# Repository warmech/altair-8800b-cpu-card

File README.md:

# Altair 8800B CPU Card
This is a reproduction of the MITS Altair 8800B CPU card, with some cleanup to trace routing and pad placement. While there are reproductions of the 8800's CPU card available, the 8800B's CPU card has not (to date) been reproduced. You may be wondering why this version of the Altair's CPU card exists and the original 8800 card is not useable; this is because the architecture of the 8800 and 8800B differ ever so slightly, making each computer's CPU card incompatible with the other without making some hardware changes.

This version of the card incorporates all of the pertinent hardware design of the original 8800B card, but leaves out all of the unnecessary and/or ancillary traces and pads that were placed for potential future development. Orphaned pads, jumpers, and vias have been removed and only two unlabeled jumpers remain in the vicinity of IC "T" near the bottom-left side of the PCB. The goal of this project was not to recreate the card in a 1:1 fashion, as the original PCB was replete with elements that served no discernably meaningful purpose. Instead, this revision offers a nice, clean, annotated PCB for those whose 8800Bs are either missing a CPU card (as mine was) or whose CPU cards are damaged beyond repair.

This design is presently untested and I am awaiting a set to be fabricated. Once I have tested this card in my 8800B, I will update this disclaimer to indicate as much.

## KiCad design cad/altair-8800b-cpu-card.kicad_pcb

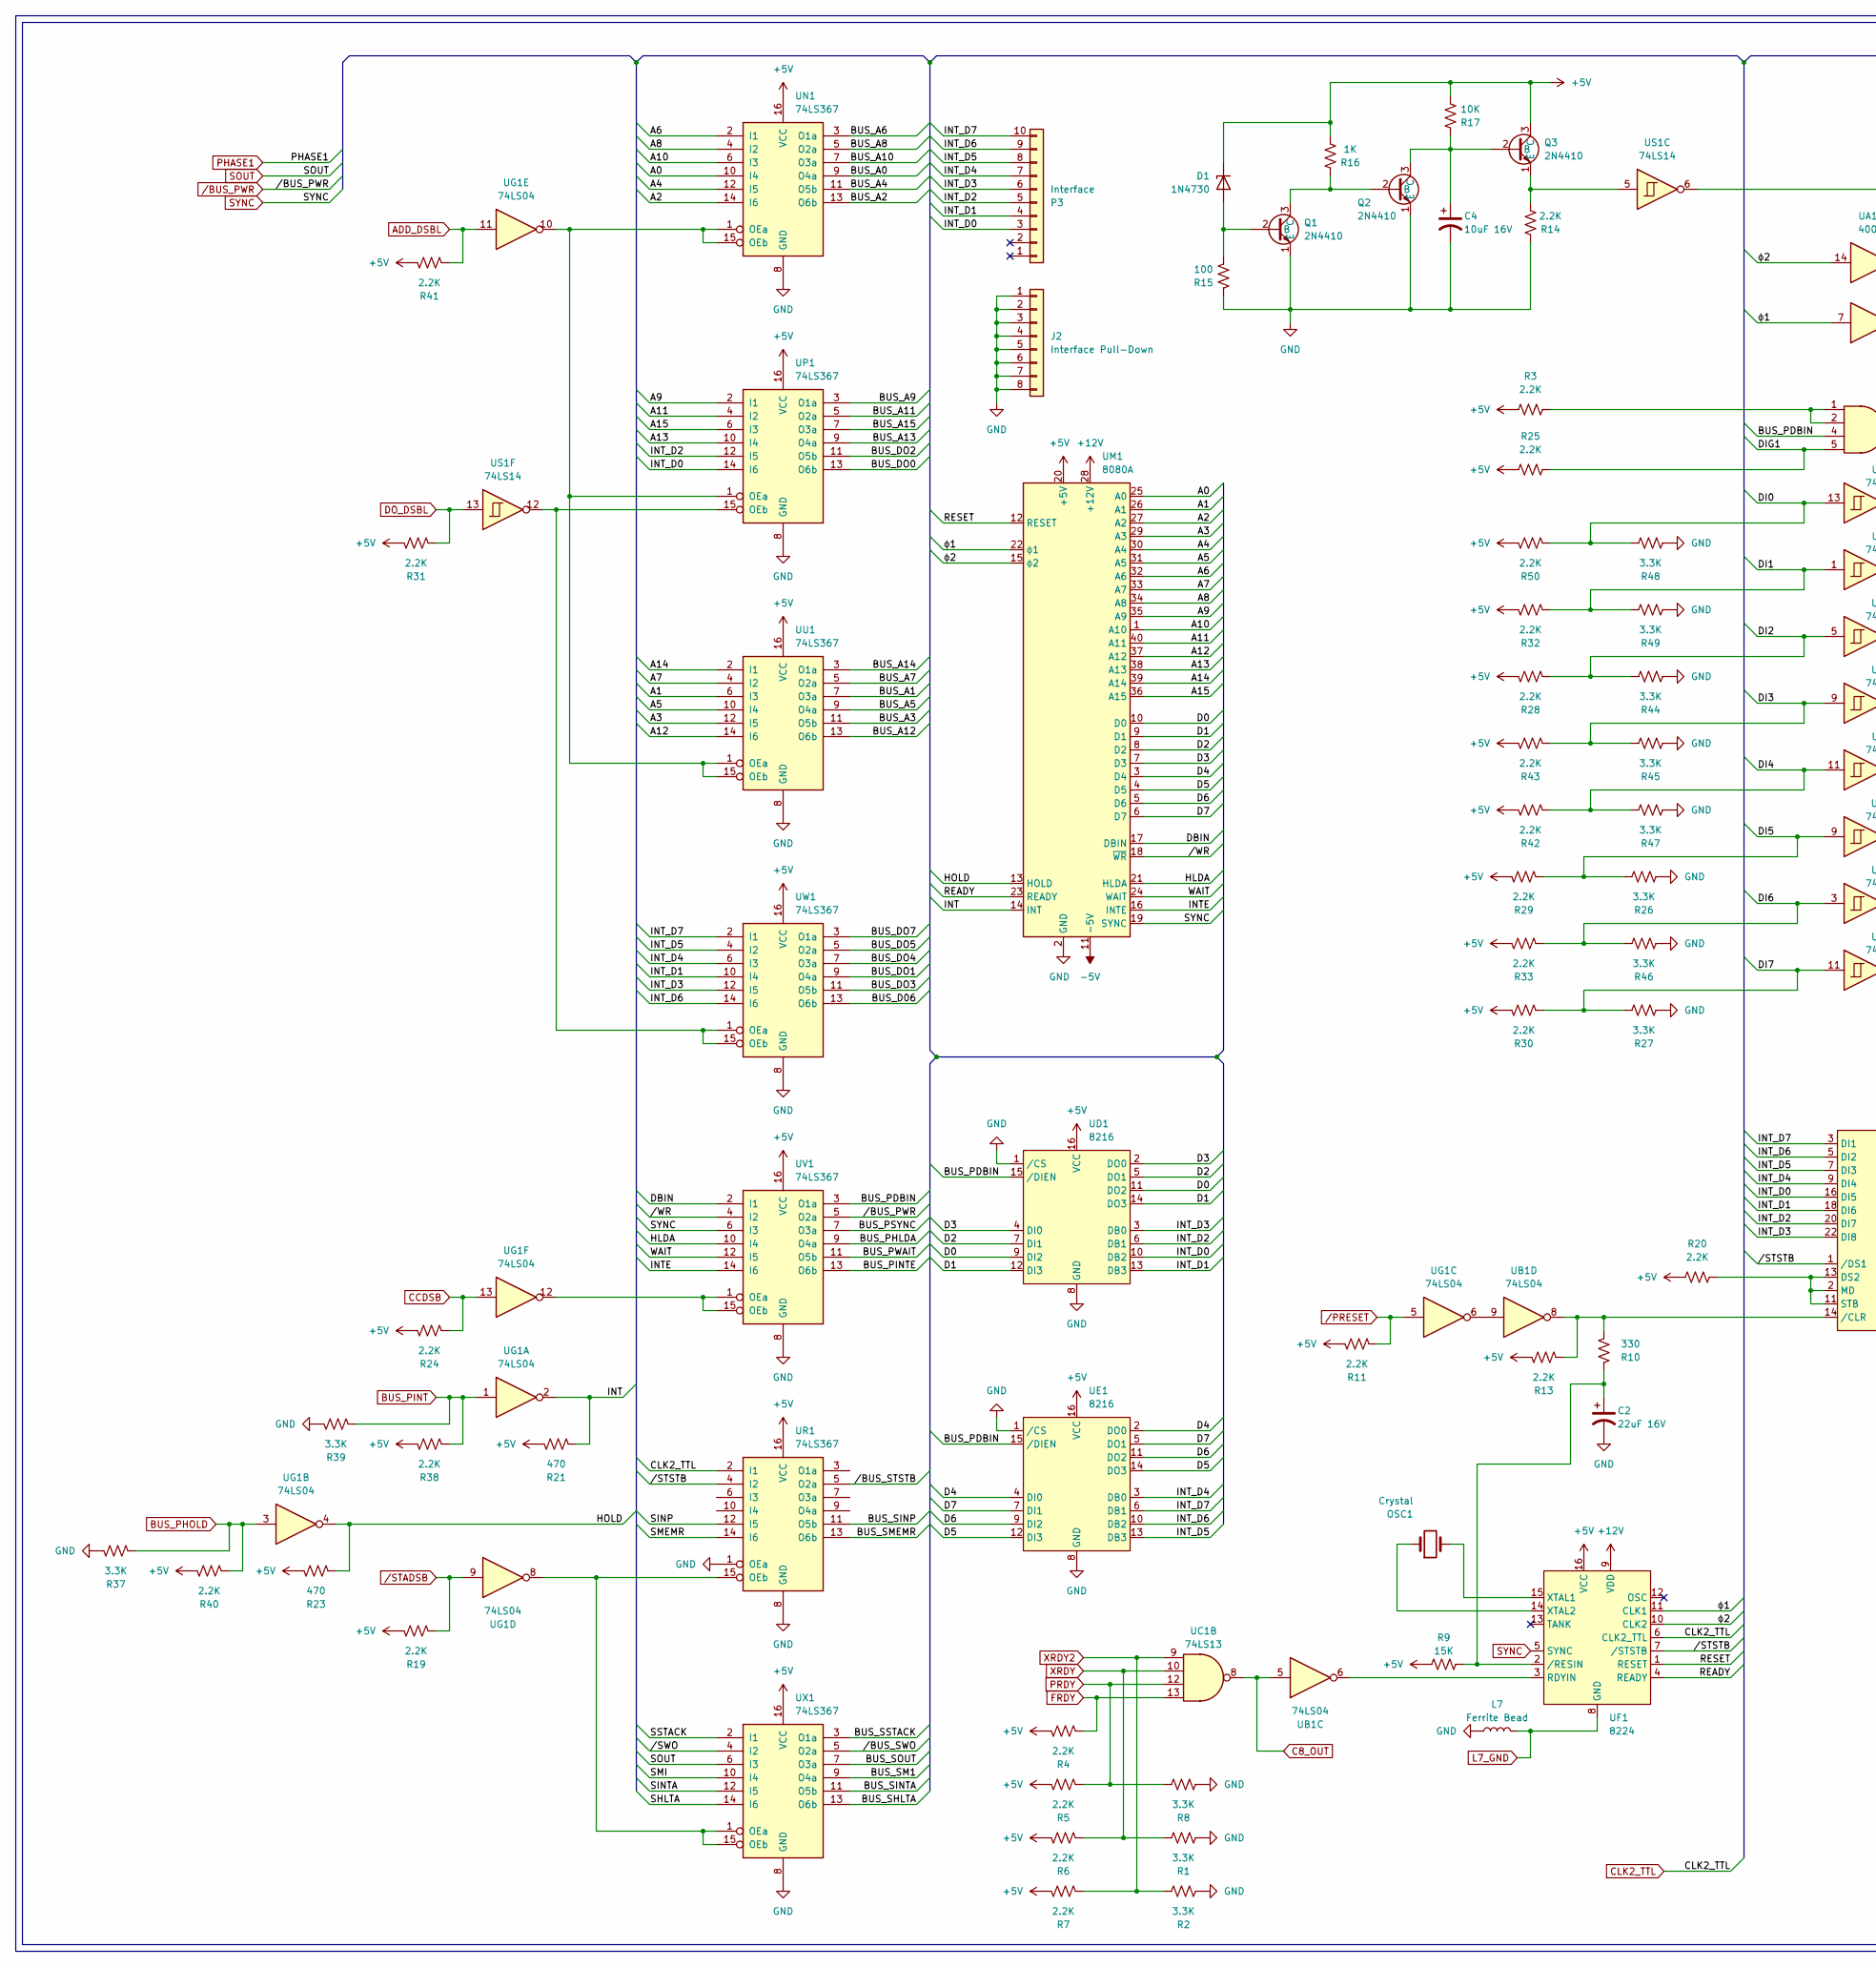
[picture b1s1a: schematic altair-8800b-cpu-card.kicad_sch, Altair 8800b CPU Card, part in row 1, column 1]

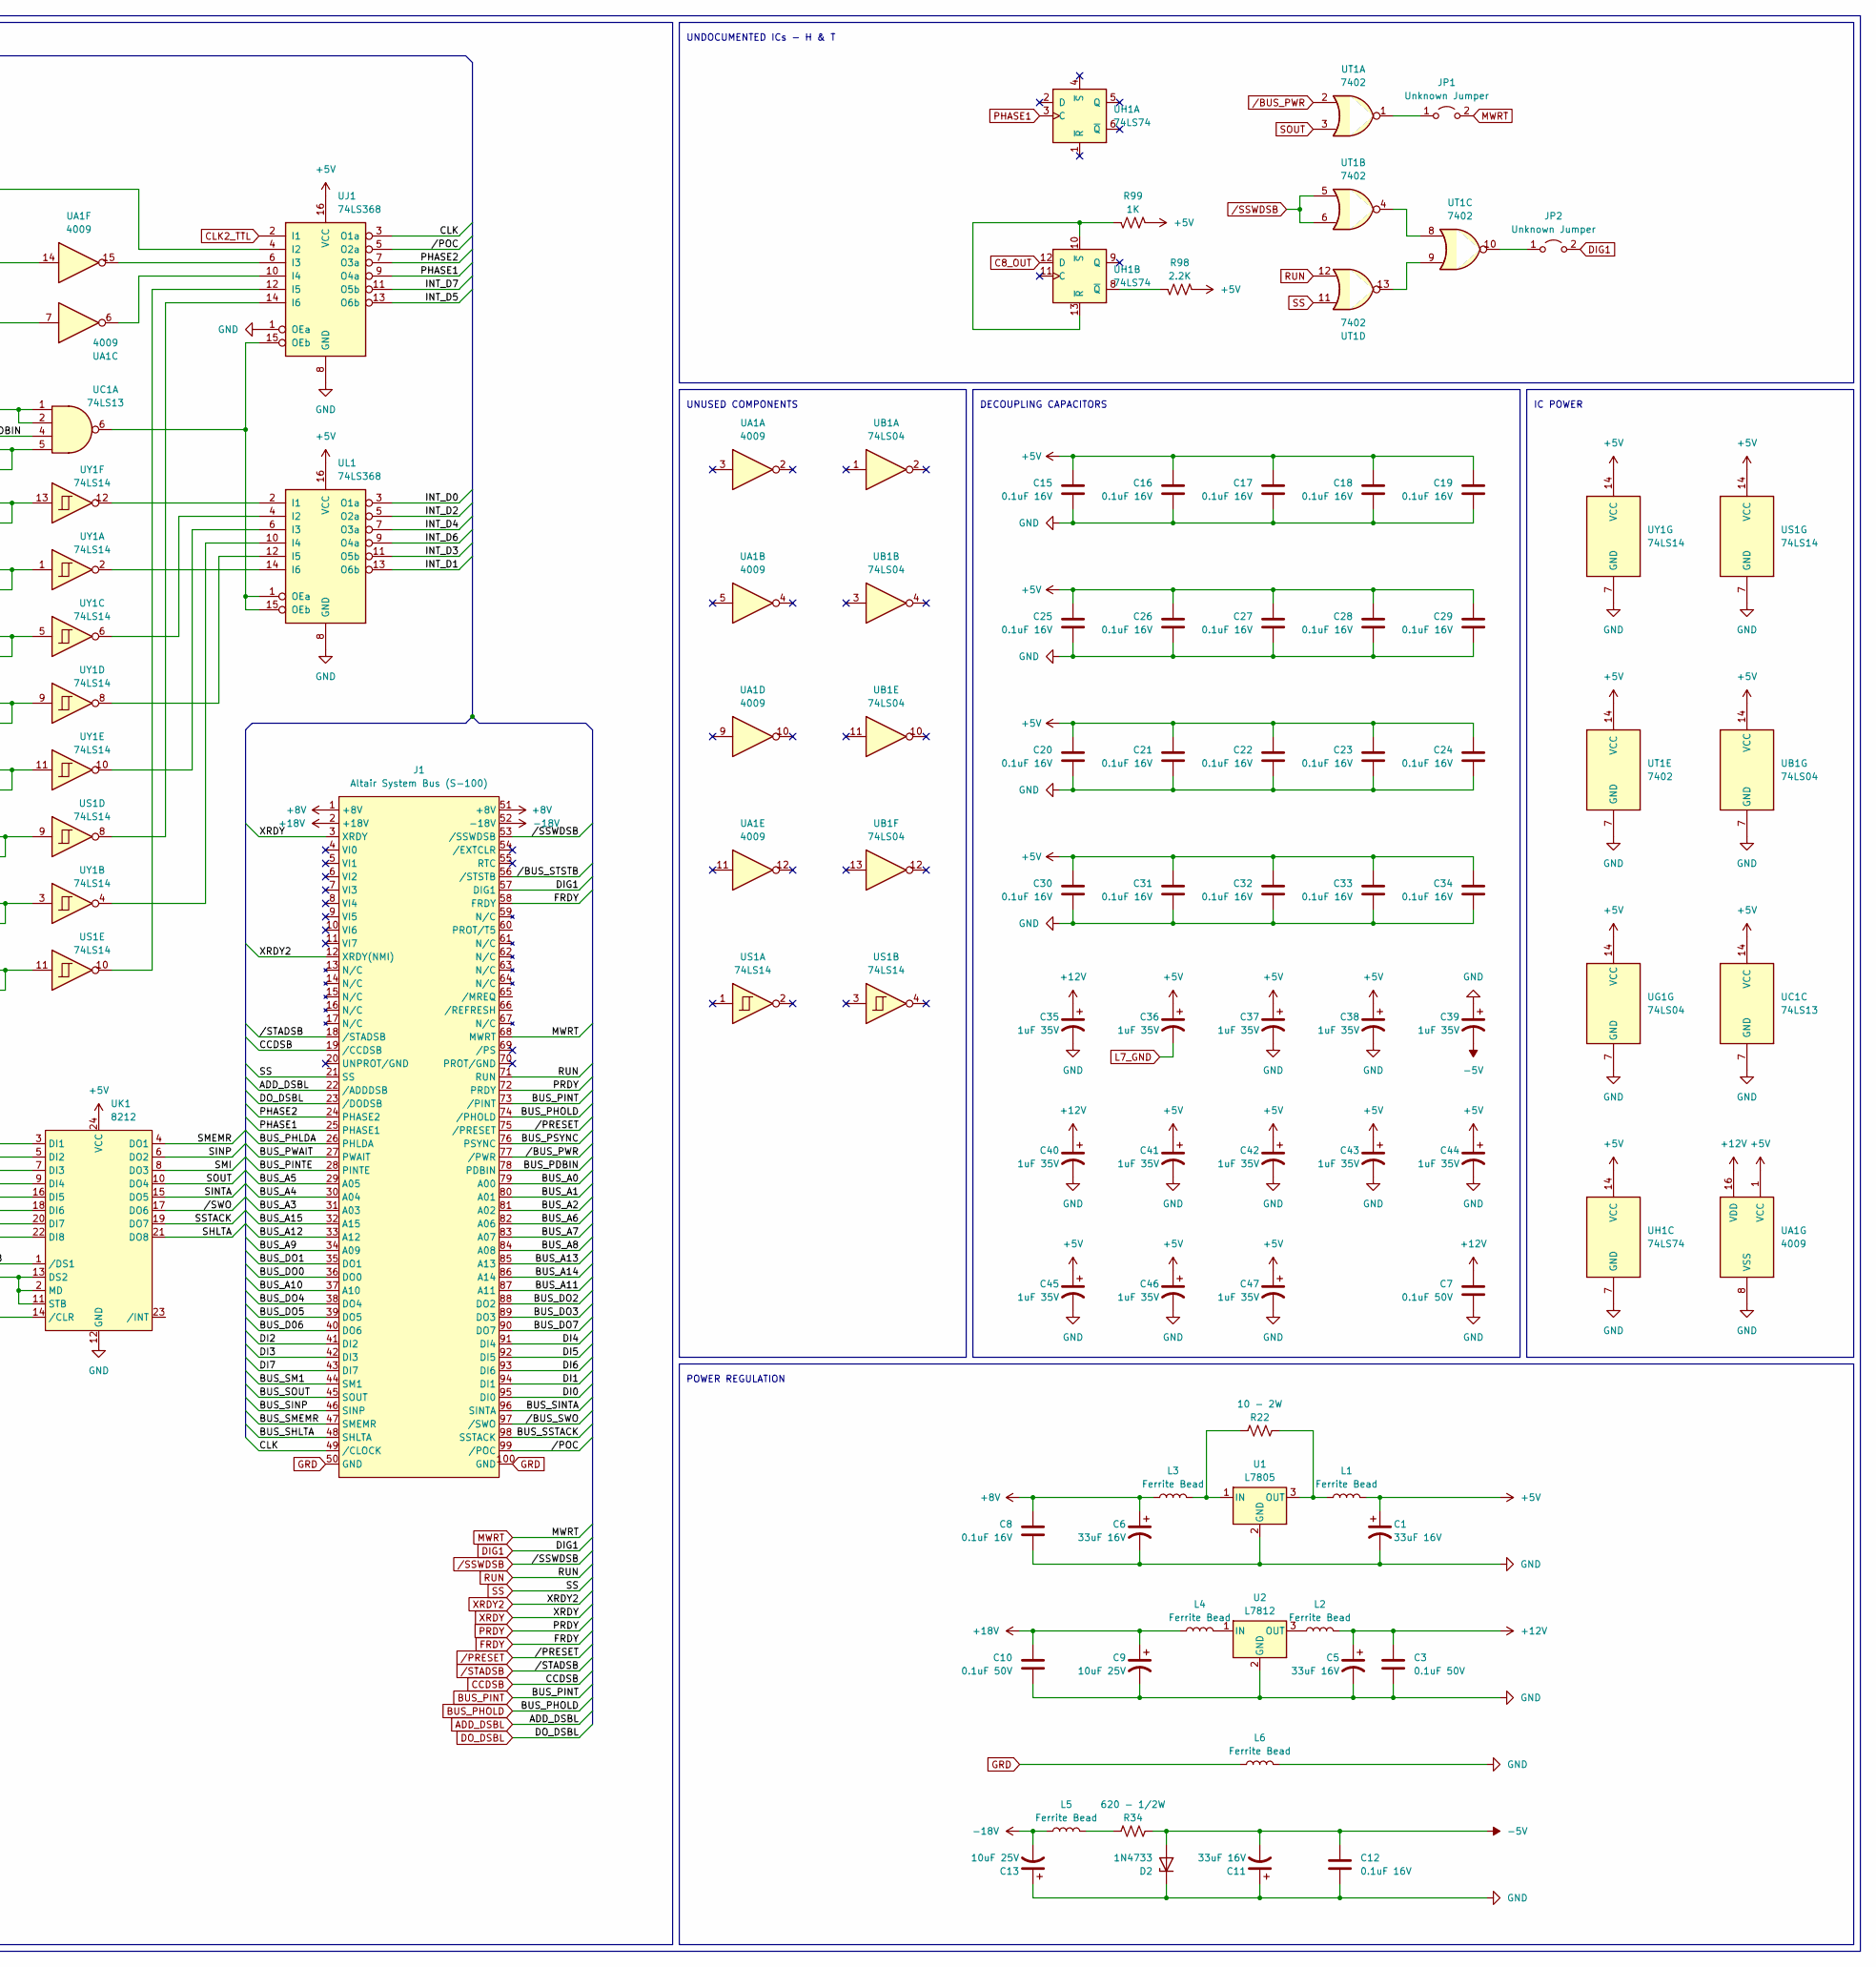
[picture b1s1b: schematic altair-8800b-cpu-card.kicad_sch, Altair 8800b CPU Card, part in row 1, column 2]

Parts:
C1, C5, C6, C11: 33uF 16V; C_Axial_L17.0mm_D6.5mm_P20.00mm_Horizontal
C2: 22uF 16V; CP_Radial_Tantal_D4.5mm_P2.50mm
C3, C7, C10: 0.1uF 50V; C_Rect_L7.0mm_W2.0mm_P5.00mm
C4: 10uF 16V; CP_Radial_Tantal_D4.5mm_P2.50mm
C8, C12, C15, C16, C17, C18, C19, C20, C21, C22, C23, C24, C25, C26, C27, C28, C29, C30, C31, C32, C33, C34: 0.1uF 16V; C_Rect_L7.0mm_W2.0mm_P5.00mm
C9, C13: 10uF 25V; C_Axial_L17.0mm_D6.5mm_P20.00mm_Horizontal
C35, C36, C37, C38, C39, C40, C41, C42, C43, C44, C45, C46, C47: 1uF 35V; CP_Radial_Tantal_D4.5mm_P2.50mm
D1: 1N4730; D_DO-41_SOD81_P10.16mm_Horizontal
D2: 1N4733; D_DO-41_SOD81_P10.16mm_Horizontal
J1: Altair System Bus (S-100); Altair_8800_Bus_Card_Edge
J2: Interface Pull-Down; PinHeader_1x08_P2.54mm_Vertical
JP1, JP2: Unknown Jumper; PinHeader_1x02_P2.54mm_Vertical
L1, L2, L3, L4, L5, L6, L7: Ferrite Bead; L_Axial_L5.3mm_D2.2mm_P7.62mm_Horizontal_Vishay_IM-1
OSC1: Crystal; Crystal_HC49-U_Horizontal
P3: Interface; PinHeader_1x10_P2.54mm_Vertical
Q1, Q2, Q3: 2N4410; TO-92
R1, R2, R8, R26, R27, R37, R39, R44, R45, R46, R47, R48, R49: 3.3K; R_Axial_DIN0207_L6.3mm_D2.5mm_P10.16mm_Horizontal
R3, R4, R5, R6, R7, R11, R13, R14, R19, R20, R24, R25, R28, R29, R30, R31, R32, R33, R38, R40, R41, R42, R43, R50, R98: 2.2K; R_Axial_DIN0207_L6.3mm_D2.5mm_P10.16mm_Horizontal
R9: 15K; R_Axial_DIN0207_L6.3mm_D2.5mm_P10.16mm_Horizontal
R10: 330; R_Axial_DIN0207_L6.3mm_D2.5mm_P10.16mm_Horizontal
R15: 100; R_Axial_DIN0207_L6.3mm_D2.5mm_P10.16mm_Horizontal
R16, R99: 1K; R_Axial_DIN0207_L6.3mm_D2.5mm_P10.16mm_Horizontal
R17: 10K; R_Axial_DIN0207_L6.3mm_D2.5mm_P10.16mm_Horizontal
R21, R23: 470; R_Axial_DIN0207_L6.3mm_D2.5mm_P10.16mm_Horizontal
R22: 10 - 2W; R_Axial_DIN0918_L18.0mm_D9.0mm_P25.40mm_Horizontal
R34: 620 - 1/2W; R_Axial_DIN0207_L6.3mm_D2.5mm_P10.16mm_Horizontal
U1: L7805; TO-220-3_Horizontal_TabDown
U2: L7812; TO-220-3_Horizontal_TabDown
UA1: 4009; DIP-16_W7.62mm
UB1: 74LS04; DIP-14_W7.62mm
UC1: 74LS13; DIP-14_W7.62mm
UD1: 8216; DIP-16_W7.62mm
UE1: 8216; DIP-16_W7.62mm
UF1: 8224; DIP-16_W7.62mm
UG1: 74LS04; DIP-14_W7.62mm
UH1: 74LS74; DIP-14_W7.62mm
UJ1: 74LS368; DIP-16_W7.62mm
UK1: 8212; DIP-24_W15.24mm
UL1: 74LS368; DIP-16_W7.62mm
UM1: 8080A; DIP-40_W15.24mm
UN1: 74LS367; DIP-16_W7.62mm
UP1: 74LS367; DIP-16_W7.62mm
UR1: 74LS367; DIP-16_W7.62mm
US1: 74LS14; DIP-14_W7.62mm
UT1: 7402; DIP-14_W7.62mm
UU1: 74LS367; DIP-16_W7.62mm
UV1: 74LS367; DIP-16_W7.62mm
UW1: 74LS367; DIP-16_W7.62mm
UX1: 74LS367; DIP-16_W7.62mm
UY1: 74LS14; DIP-14_W7.62mm

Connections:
+5V: C1.1, C15.1, C16.1, C17.1, C18.1, C19.1, C20.1, C21.1, C22.1, C23.1, C24.1, C25.1, C26.1, C27.1, C28.1, C29.1, C30.1, C31.1, C32.1, C33.1, C34.1, C36.1, C37.1, C38.1, C41.1, C42.1, C43.1, C44.1, C45.1, C46.1, C47.1, D1.1 (K), L1.2, Q3.3 (C), R3.1, R4.1, R5.1, R6.1, R7.1, R9.1, R11.1, R13.1, R16.1, R17.1, R19.1, R20.1, R21.1, R23.1, R24.1, R25.1, R28.1, R29.1, R30.1, R31.1, R32.1, R33.1, R38.1, R40.1, R41.1, R42.1, R43.1, R50.1, R98.1, R99.1, UA1.1 (VCC), UB1.14 (VCC), UC1.14 (VCC), UD1.16 (VCC), UE1.16 (VCC), UF1.16 (VCC), UG1.14 (VCC), UH1.14 (VCC), UJ1.16 (VCC), UK1.24 (VCC), UL1.16 (VCC), UM1.20 (+5V), UN1.16 (VCC), UP1.16 (VCC), UR1.16 (VCC), US1.14 (VCC), UT1.14 (VCC), UU1.16 (VCC), UV1.16 (VCC), UW1.16 (VCC), UX1.16 (VCC), UY1.14 (VCC)
+8V: C6.1, C8.1, J1.1 (+8V), J1.51 (+8V), L3.1
+12V: C3.1, C5.1, C7.1, C35.1, C40.1, L2.2, UA1.16 (VDD), UF1.9 (VDD), UM1.28 (+12V)
+18V: C9.1, C10.1, J1.2 (+18V), L4.1
-5V: C11.2, C12.1, C39.2, D2.2 (A), R34.2, UM1.11 (-5V)
-18V: C13.2, J1.52 (-18V), L5.1
/A0: UM1.25 (A0), UN1.10 (I4)
/A1: UM1.26 (A1), UU1.6 (I3)
/A2: UM1.27 (A2), UN1.14 (I6)
/A3: UM1.29 (A3), UU1.12 (I5)
/A4: UM1.30 (A4), UN1.12 (I5)
/A5: UM1.31 (A5), UU1.10 (I4)
/A6: UM1.32 (A6), UN1.2 (I1)
/A7: UM1.33 (A7), UU1.4 (I2)
/A8: UM1.34 (A8), UN1.4 (I2)
/A9: UM1.35 (A9), UP1.2 (I1)
/A10: UM1.1 (A10), UN1.6 (I3)
/A11: UM1.40 (A11), UP1.4 (I2)
/A12: UM1.37 (A12), UU1.14 (I6)
/A13: UM1.38 (A13), UP1.10 (I4)
/A14: UM1.39 (A14), UU1.2 (I1)
/A15: UM1.36 (A15), UP1.6 (I3)
/BUS_A0: J1.79 (A00), UN1.9 (O4a)
/BUS_A1: J1.80 (A01), UU1.7 (O3a)
/BUS_A2: J1.81 (A02), UN1.13 (O6b)
/BUS_A3: J1.31 (A03), UU1.11 (O5b)
/BUS_A4: J1.30 (A04), UN1.11 (O5b)
/BUS_A5: J1.29 (A05), UU1.9 (O4a)
/BUS_A6: J1.82 (A06), UN1.3 (O1a)
/BUS_A7: J1.83 (A07), UU1.5 (O2a)
/BUS_A8: J1.84 (A08), UN1.5 (O2a)
/BUS_A9: J1.34 (A09), UP1.3 (O1a)
/BUS_A10: J1.37 (A10), UN1.7 (O3a)
/BUS_A11: J1.87 (A11), UP1.5 (O2a)
/BUS_A12: J1.33 (A12), UU1.13 (O6b)
/BUS_A13: J1.85 (A13), UP1.9 (O4a)
/BUS_A14: J1.86 (A14), UU1.3 (O1a)
/BUS_A15: J1.32 (A15), UP1.7 (O3a)
/BUS_D06: J1.40 (DO6), UW1.13 (O6b)
/BUS_DO0: J1.36 (DO0), UP1.13 (O6b)
/BUS_DO1: J1.35 (DO1), UW1.9 (O4a)
/BUS_DO2: J1.88 (DO2), UP1.11 (O5b)
/BUS_DO3: J1.89 (DO3), UW1.11 (O5b)
/BUS_DO4: J1.38 (DO4), UW1.7 (O3a)
/BUS_DO5: J1.39 (DO5), UW1.5 (O2a)
/BUS_DO7: J1.90 (DO7), UW1.3 (O1a)
/BUS_PDBIN: J1.78 (PDBIN), UC1.4, UD1.15 (/DIEN), UE1.15 (/DIEN), UV1.3 (O1a)
/BUS_PHLDA: J1.26 (PHLDA), UV1.9 (O4a)
/BUS_PINTE: J1.28 (PINTE), UV1.13 (O6b)
/BUS_PSYNC: J1.76 (PSYNC), UV1.7 (O3a)
/BUS_PWAIT: J1.27 (PWAIT), UV1.11 (O5b)
/BUS_SHLTA: J1.48 (SHLTA), UX1.13 (O6b)
/BUS_SINP: J1.46 (SINP), UR1.11 (O5b)
/BUS_SINTA: J1.96 (SINTA), UX1.11 (O5b)
/BUS_SM1: J1.44 (SM1), UX1.9 (O4a)
/BUS_SMEMR: J1.47 (SMEMR), UR1.13 (O6b)
/BUS_SOUT: J1.45 (SOUT), UX1.7 (O3a)
/BUS_SSTACK: J1.98 (SSTACK), UX1.3 (O1a)
/CLK: J1.49 (/CLOCK), UJ1.3 (O1a)
/D0: UD1.9 (DI2), UD1.11 (DO2), UM1.10 (D0)
/D1: UD1.12 (DI3), UD1.14 (DO3), UM1.9 (D1)
/D2: UD1.5 (DO1), UD1.7 (DI1), UM1.8 (D2)
/D3: UD1.2 (DO0), UD1.4 (DI0), UM1.7 (D3)
/D4: UE1.2 (DO0), UE1.4 (DI0), UM1.3 (D4)
/D5: UE1.12 (DI3), UE1.14 (DO3), UM1.4 (D5)
/D6: UE1.9 (DI2), UE1.11 (DO2), UM1.5 (D6)
/D7: UE1.5 (DO1), UE1.7 (DI1), UM1.6 (D7)
/DBIN: UM1.17 (DBIN), UV1.2 (I1)
/DI0: J1.95 (DI0), R48.2, R50.2, UY1.13
/DI1: J1.94 (DI1), R32.2, R49.2, UY1.1
/DI2: J1.41 (DI2), R28.2, R44.2, UY1.5
/DI3: J1.42 (DI3), R43.2, R45.2, UY1.9
/DI4: J1.91 (DI4), R42.2, R47.2, UY1.11
/DI5: J1.92 (DI5), R26.2, R29.2, US1.9
/DI6: J1.93 (DI6), R33.2, R46.2, UY1.3
/DI7: J1.43 (DI7), R27.2, R30.2, US1.11
/HLDA: UM1.21 (HLDA), UV1.10 (I4)
/HOLD: R23.2, UG1.4, UM1.13 (HOLD)
/INT: R21.2, UG1.2, UM1.14 (INT)
/INTE: UM1.16 (INTE), UV1.14 (I6)
/INT_D0: P3.3, UD1.10 (DB2), UK1.16 (DI5), UL1.3 (O1a), UP1.14 (I6)
/INT_D1: P3.4, UD1.13 (DB3), UK1.18 (DI6), UL1.13 (O6b), UW1.10 (I4)
/INT_D2: P3.5, UD1.6 (DB1), UK1.20 (DI7), UL1.5 (O2a), UP1.12 (I5)
/INT_D3: P3.6, UD1.3 (DB0), UK1.22 (DI8), UL1.11 (O5b), UW1.12 (I5)
/INT_D4: P3.7, UE1.3 (DB0), UK1.9 (DI4), UL1.7 (O3a), UW1.6 (I3)
/INT_D5: P3.8, UE1.13 (DB3), UJ1.13 (O6b), UK1.7 (DI3), UW1.4 (I2)
/INT_D6: P3.9, UE1.10 (DB2), UK1.5 (DI2), UL1.9 (O4a), UW1.14 (I6)
/INT_D7: P3.10, UE1.6 (DB1), UJ1.11 (O5b), UK1.3 (DI1), UW1.2 (I1)
/PHASE2: J1.24 (PHASE2), UJ1.7 (O3a)
/READY: UF1.4 (READY), UM1.23 (READY)
/RESET: UF1.1 (RESET), UM1.12 (RESET)
/SHLTA: UK1.21 (DO8), UX1.14 (I6)
/SINP: UK1.6 (DO2), UR1.12 (I5)
/SINTA: UK1.15 (DO5), UX1.12 (I5)
/SMEMR: UK1.4 (DO1), UR1.14 (I6)
/SMI: UK1.8 (DO3), UX1.10 (I4)
/SSTACK: UK1.19 (DO7), UX1.2 (I1)
/WAIT: UM1.24 (WAIT), UV1.12 (I5)
//BUS_STSTB: J1.56 (/STSTB), UR1.5 (O2a)
//BUS_SWO: J1.97 (/SWO), UX1.5 (O2a)
//POC: J1.99 (/POC), UJ1.5 (O2a)
//STSTB: UF1.7 (/STSTB), UK1.1 (/DS1), UR1.4 (I2)
//SWO: UK1.17 (DO6), UX1.4 (I2)
//WR: UM1.18 (~WR), UV1.4 (I2)
/ϕ1: UA1.7, UF1.11 (CLK1), UM1.22 (ϕ1)
/ϕ2: UA1.14, UF1.10 (CLK2), UM1.15 (ϕ2)
ADD_DSBL: J1.22 (/ADDDSB), R41.2, UG1.11
BUS_PHOLD: J1.74 (/PHOLD), R37.2, R40.2, UG1.3
BUS_PINT: J1.73 (/PINT), R38.2, R39.2, UG1.1
C8_OUT: UB1.5, UC1.8, UH1.12 (D)
CCDSB: J1.19 (/CCDSB), R24.2, UG1.13
CLK2_TTL: UF1.6 (CLK2_TTL), UJ1.2 (I1), UR1.2 (I1)
DIG1: J1.57 (DIG1), JP2.2 (B), R25.2, UC1.5
DO_DSBL: J1.23 (/DODSB), R31.2, US1.13
FRDY: J1.58 (FRDY), R4.2, UC1.13
GND: C1.2, C2.2, C3.2, C4.2, C5.2, C6.2, C7.2, C8.2, C9.2, C10.2, C11.1, C12.2, C13.1, C15.2, C16.2, C17.2, C18.2, C19.2, C20.2, C21.2, C22.2, C23.2, C24.2, C25.2, C26.2, C27.2, C28.2, C29.2, C30.2, C31.2, C32.2, C33.2, C34.2, C35.2, C37.2, C38.2, C39.1, C40.2, C41.2, C42.2, C43.2, C44.2, C45.2, C46.2, C47.2, D2.1 (K), J2.1, J2.2, J2.3, J2.4, J2.5, J2.6, J2.7, J2.8, L6.2, L7.1, Q1.1 (E), Q2.1 (E), R1.1, R2.1, R8.1, R14.2, R15.2, R26.1, R27.1, R37.1, R39.1, R44.1, R45.1, R46.1, R47.1, R48.1, R49.1, U1.2 (GND), U2.2 (GND), UA1.8 (VSS), UB1.7 (GND), UC1.7 (GND), UD1.1 (/CS), UD1.8 (GND), UE1.1 (/CS), UE1.8 (GND), UG1.7 (GND), UH1.7 (GND), UJ1.1 (OEa), UJ1.8 (GND), UK1.12 (GND), UL1.8 (GND), UM1.2 (GND), UN1.8 (GND), UP1.8 (GND), UR1.1 (OEa), UR1.8 (GND), US1.7 (GND), UT1.7 (GND), UU1.8 (GND), UV1.8 (GND), UW1.8 (GND), UX1.8 (GND), UY1.7 (GND)
GRD: J1.50 (GND), J1.100 (GND), L6.1
L7_GND: C36.2, L7.2, UF1.8 (GND)
MWRT: J1.68 (MWRT), JP1.2 (B)
unnamed: D1.2 (A), Q1.2 (B), R15.1
unnamed: JP1.1 (A), UT1.1
unnamed: JP2.1 (A), UT1.10
unnamed: L5.2, R34.1
unnamed: Q1.3 (C), Q2.2 (B), R16.2
unnamed: C4.1, Q2.3 (C), Q3.2 (B), R17.2
unnamed: Q3.1 (E), R14.1, US1.5
unnamed: R3.2, UC1.1, UC1.2
unnamed: L3.2, R22.1, U1.1 (IN)
unnamed: L1.1, R22.2, U1.3 (OUT)
unnamed: L4.2, U2.1 (IN)
unnamed: L2.1, U2.3 (OUT)
unnamed: UB1.9, UG1.6
unnamed: UB1.6, UF1.3 (RDYIN)
unnamed: OSC1.2, UF1.15 (XTAL1)
unnamed: OSC1.1, UF1.14 (XTAL2)
unnamed: C2.1, R9.2, R10.1, UF1.2 (/RESIN)
unnamed: R98.2, UH1.8 (~Q)
unnamed: R99.2, UH1.10 (~S), UH1.13 (~R)
unnamed: UJ1.4 (I2), US1.6
unnamed: UA1.15, UJ1.6 (I3)
unnamed: UA1.6, UJ1.10 (I4)
unnamed: UJ1.12 (I5), US1.10
unnamed: UJ1.14 (I6), US1.8
unnamed: UC1.6, UJ1.15 (OEb), UL1.1 (OEa), UL1.15 (OEb)
unnamed: R20.2, UK1.2 (MD), UK1.11 (STB), UK1.13 (DS2)
unnamed: R10.2, R13.2, UB1.8, UK1.14 (/CLR)
unnamed: UL1.2 (I1), UY1.12
unnamed: UL1.4 (I2), UY1.6
unnamed: UL1.6 (I3), UY1.10
unnamed: UL1.10 (I4), UY1.4
unnamed: UL1.12 (I5), UY1.8
unnamed: UL1.14 (I6), UY1.2
unnamed: UG1.10, UN1.1 (OEa), UN1.15 (OEb), UP1.1 (OEa), UU1.1 (OEa), UU1.15 (OEb)
unnamed: UP1.15 (OEb), US1.12, UW1.1 (OEa), UW1.15 (OEb)
unnamed: UG1.8, UR1.15 (OEb), UX1.1 (OEa), UX1.15 (OEb)
unnamed: UT1.4, UT1.8
unnamed: UT1.9, UT1.13
unnamed: UG1.12, UV1.1 (OEa), UV1.15 (OEb)
PHASE1: J1.25 (PHASE1), UH1.3 (C), UJ1.9 (O4a)
PRDY: J1.72 (PRDY), R5.2, R8.2, UC1.12
RUN: J1.71 (RUN), UT1.12
SOUT: UK1.10 (DO4), UT1.3, UX1.6 (I3)
SS: J1.21 (SS), UT1.11
SYNC: UF1.5 (SYNC), UM1.19 (SYNC), UV1.6 (I3)
XRDY: J1.3 (XRDY), R1.2, R6.2, UC1.10
XRDY2: J1.12 (XRDY(NMI)), R2.2, R7.2, UC1.9
/BUS_PWR: J1.77 (/PWR), UT1.2, UV1.5 (O2a)
/PRESET: J1.75 (/PRESET), R11.2, UG1.5
/SSWDSB: J1.53 (/SSWDSB), UT1.5, UT1.6
/STADSB: J1.18 (/STADSB), R19.2, UG1.9

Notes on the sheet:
DECOUPLING CAPACITORS
POWER REGULATION
IC POWER
UNUSED COMPONENTS
UNDOCUMENTED ICs - H & T

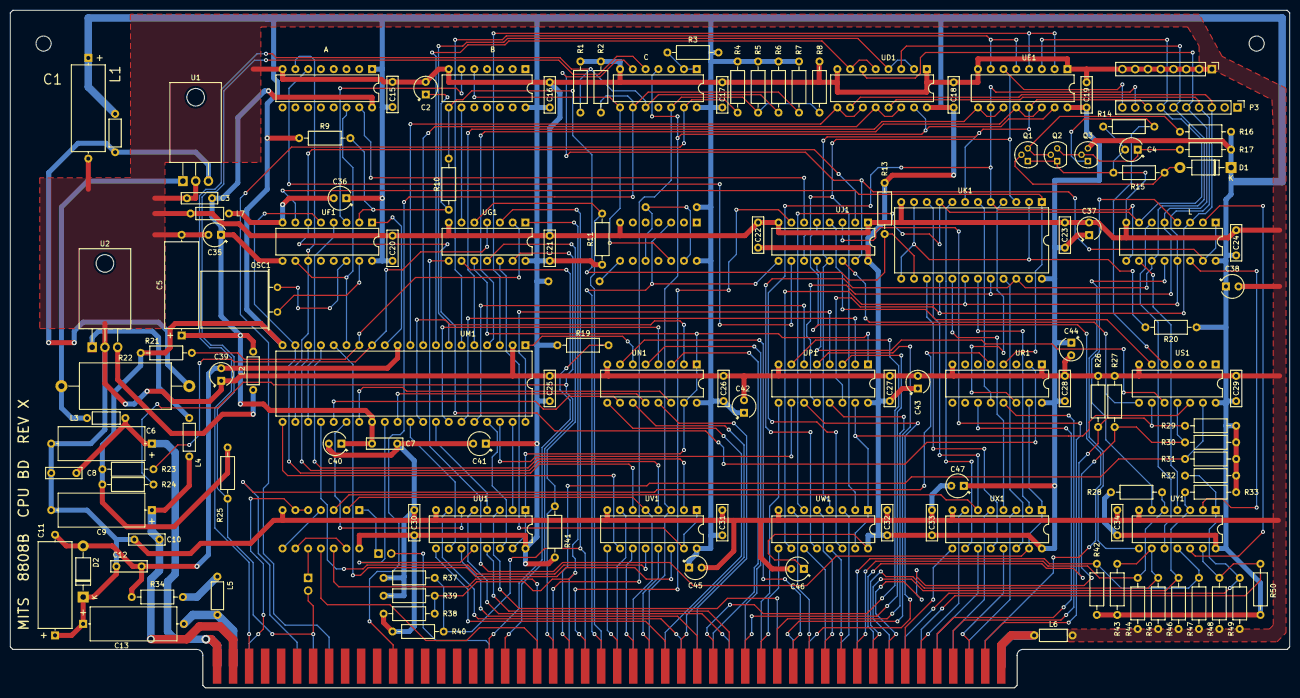
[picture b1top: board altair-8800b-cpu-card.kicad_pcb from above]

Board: 2 copper layers, 254.2 x 134.6 mm, 136 parts (0 on the bottom side), 170 nets.

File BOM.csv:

"Source:","C:\Users\wtooker\GitHub\altair-8800b-cpu-card\cad\altair-8800b-cpu-card.kicad_sch"
"Date:","11/8/2024 1:40:58 PM"
"Tool:","Eeschema 7.0.8"
"Generator:","C:\Program Files\KiCad\7.0\bin\scripting\plugins/bom_csv_grouped_by_value.py"
"Component Count:","136"

"Collated Components:"

"Item","Qty","Reference(s)","Value","LibPart","Footprint","Datasheet","DNP"
"1","4","C1, C5, C6, C11","33uF 16V","Device:C_Polarized_US","Capacitor_THT_Custom:C_Axial_L17.0mm_D6.5mm_P20.00mm_Horizontal","~",""
"2","1","C2","22uF 16V","Device:C_Polarized_US","Capacitor_THT:CP_Radial_Tantal_D4.5mm_P2.50mm","~",""
"3","3","C3, C7, C10","0.1uF 50V","Device:C","Capacitor_THT:C_Rect_L7.0mm_W2.0mm_P5.00mm","~",""
"4","1","C4","10uF 16V","Device:C_Polarized_US","Capacitor_THT:CP_Radial_Tantal_D4.5mm_P2.50mm","~",""
"5","22","C8, C12, C15, C16, C17, C18, C19, C20, C21, C22, C23, C24, C25, C26, C27, C28, C29, C30, C31, C32, C33, C34","0.1uF 16V","Device:C","Capacitor_THT:C_Rect_L7.0mm_W2.0mm_P5.00mm","~",""
"6","2","C9, C13","10uF 25V","Device:C_Polarized_US","Capacitor_THT_Custom:C_Axial_L17.0mm_D6.5mm_P20.00mm_Horizontal","~",""
"7","13","C35, C36, C37, C38, C39, C40, C41, C42, C43, C44, C45, C46, C47","1uF 35V","Device:C_Polarized_US","Capacitor_THT:CP_Radial_Tantal_D4.5mm_P2.50mm","~",""
"8","1","D1","1N4730","Diode:1N47xxA","Diode_THT:D_DO-41_SOD81_P10.16mm_Horizontal","https://www.vishay.com/docs/85816/1n4728a.pdf",""
"9","1","D2","1N4733","Diode:1N47xxA","Diode_THT:D_DO-41_SOD81_P10.16mm_Horizontal","https://www.vishay.com/docs/85816/1n4728a.pdf",""
"10","1","J1","Altair System Bus (S-100)","Connector_Custom:MITS_Altair_Bus_CardEdge","Connector_Custom:Altair_8800_Bus_Card_Edge","",""
"11","1","J2","Interface Pull-Down","Connector_Generic:Conn_01x08","Connector_PinHeader_2.54mm:PinHeader_1x08_P2.54mm_Vertical","~",""
"12","2","JP1, JP2","Unknown Jumper","Jumper:Jumper_2_Open","Connector_PinHeader_2.54mm:PinHeader_1x02_P2.54mm_Vertical","~",""
"13","7","L1, L2, L3, L4, L5, L6, L7","Ferrite Bead","Device:L","Inductor_THT:L_Axial_L5.3mm_D2.2mm_P7.62mm_Horizontal_Vishay_IM-1","~",""
"14","1","OSC1","Crystal","Device:Crystal","Crystal:Crystal_HC49-U_Horizontal","~",""
"15","1","P3","Interface","Connector_Generic:Conn_01x10","Connector_PinHeader_2.54mm:PinHeader_1x10_P2.54mm_Vertical","~",""
"16","3","Q1, Q2, Q3","2N4410","Transistor_Custom:2N4410","Package_TO_SOT_THT:TO-92","",""
"17","13","R1, R2, R8, R26, R27, R37, R39, R44, R45, R46, R47, R48, R49","3.3K","Device:R_US","Resistor_THT:R_Axial_DIN0207_L6.3mm_D2.5mm_P10.16mm_Horizontal","~",""
"18","25","R3, R4, R5, R6, R7, R11, R13, R14, R19, R20, R24, R25, R28, R29, R30, R31, R32, R33, R38, R40, R41, R42, R43, R50, R98","2.2K","Device:R_US","Resistor_THT:R_Axial_DIN0207_L6.3mm_D2.5mm_P10.16mm_Horizontal","~",""
"19","1","R9","15K","Device:R_US","Resistor_THT:R_Axial_DIN0207_L6.3mm_D2.5mm_P10.16mm_Horizontal","~",""
"20","1","R10","330","Device:R_US","Resistor_THT:R_Axial_DIN0207_L6.3mm_D2.5mm_P10.16mm_Horizontal","~",""
"21","1","R15","100","Device:R_US","Resistor_THT:R_Axial_DIN0207_L6.3mm_D2.5mm_P10.16mm_Horizontal","~",""
"22","2","R16, R99","1K","Device:R_US","Resistor_THT:R_Axial_DIN0207_L6.3mm_D2.5mm_P10.16mm_Horizontal","~",""
"23","1","R17","10K","Device:R_US","Resistor_THT:R_Axial_DIN0207_L6.3mm_D2.5mm_P10.16mm_Horizontal","~",""
"24","2","R21, R23","470","Device:R_US","Resistor_THT:R_Axial_DIN0207_L6.3mm_D2.5mm_P10.16mm_Horizontal","~",""
"25","1","R22","10 - 2W","Device:R_US","Resistor_THT:R_Axial_DIN0918_L18.0mm_D9.0mm_P25.40mm_Horizontal","~",""
"26","1","R34","620 - 1/2W","Device:R_US","Resistor_THT:R_Axial_DIN0207_L6.3mm_D2.5mm_P10.16mm_Horizontal","~",""
"27","1","U1","L7805","Regulator_Linear:L7805","Package_TO_SOT_THT:TO-220-3_Horizontal_TabDown","http://www.st.com/content/ccc/resource/technical/document/da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",""
"28","1","U2","L7812","Regulator_Linear:L7812","Package_TO_SOT_THT:TO-220-3_Horizontal_TabDown","http://www.st.com/content/ccc/resource/technical/document/da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",""
"29","1","UA1","4009","4xxx:4009","Package_DIP:DIP-16_W7.62mm","http://www.sycelectronica.com.ar/semiconductores/CD4009.pdf",""
"30","2","UB1, UG1","74LS04","74xx:74LS04","Package_DIP:DIP-14_W7.62mm","http://www.ti.com/lit/gpn/sn74LS04",""
"31","1","UC1","74LS13","74xx:74LS13","Package_DIP:DIP-14_W7.62mm","http://www.ti.com/lit/gpn/sn74LS13",""
"32","2","UD1, UE1","8216","8xxx_Custom:8216","Package_DIP:DIP-16_W7.62mm","",""
"33","1","UF1","8224","8xxx_Custom:8224","Package_DIP:DIP-16_W7.62mm","",""
"34","1","UH1","74LS74",":74LS74_1","Package_DIP:DIP-14_W7.62mm","74xx/74hc_hct74.pdf",""
"35","2","UJ1, UL1","74LS368","74xx:74LS368","Package_DIP:DIP-16_W7.62mm","http://www.ti.com/lit/gpn/sn74LS368",""
"36","1","UK1","8212","8xxx_Custom:8212","Package_DIP:DIP-24_W15.24mm","",""
"37","1","UM1","8080A","MCU_Intel:8080A","Package_DIP:DIP-40_W15.24mm","http://datasheets.chipdb.org/Intel/MCS-80/intel-8080.pdf",""
"38","7","UN1, UP1, UR1, UU1, UV1, UW1, UX1","74LS367","74xx:74LS367","Package_DIP:DIP-16_W7.62mm","http://www.ti.com/lit/gpn/sn74LS367",""
"39","2","US1, UY1","74LS14","74xx:74LS14","Package_DIP:DIP-14_W7.62mm","http://www.ti.com/lit/gpn/sn74LS14",""
"40","1","UT1","7402","74xx:7402","Package_DIP:DIP-14_W7.62mm","http://www.ti.com/lit/gpn/sn7402",""

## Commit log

2024-10-31 Initial release
2024-11-02 Added miters to PCB corners
2024-11-08 Generated BOM
